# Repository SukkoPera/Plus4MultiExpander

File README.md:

# Plus4MultiExpander

Plus4MultiExpander is a port expander that allows multiple boards to be connected to the Expansion port of a Commodore 16, 116 and Plus/4.

## Summary
The main problem in making an Expansion port extender for the 264 line of computers is the complete unavailability of the original connector: these machines use a 50-pin connector with 2.00 mm pitch, which is nowhere to be found. This has been a problem since the old days, as you can see that even Solder of Synergy used different connectors when he made his [Expansion Port Splitter](https://plus4world.powweb.com/hardware/Expansionport_Splitter) in 1994. He used 50-pin connectors with 2.54 mm pitch, which in turn became rather uncommon in the following years, until they recently resurfaced from Chinese sellers.

This problem with the unavailability of the connector also affects [LittleSixteen](https://github.com/SukkoPera/LittleSixteen). Since one of the goals of that project is to fit into an unmodified C64-style case, Solder's connector of choice wouldn't help, as it is much larger than the opening on the case.

Of course, the opening on the case was made for the 44-pin 2.54 mm pitch connector the C64 uses, which for some reason is still available on the market, even from reliable manufacturers. It only has 6 pins less and since some of the pins on the 264 line are not used, I decided it was the best candidate for the new Expansion connector of the 264 line of computers.

## Design Notes
### Bus Buffers
Significant inspiration for the design of the expander comes from Solder's 1994 version. In particular, the expander integrates buffers for the address bus, in order to compensate for the increased bus capacitance. No buffers seem to be required on the data bus.

### Dropped Signals
As mentioned, 50-44=6 pins need to be dropped from the original connector:
- 3 are obvious, the unused pins: Z, AA, BB
- Since it is basically impossible to make an external RAM expansion, two more obvious drops would be the pins for the `/RAS` and `/CAS` signals. Unfortunately, `/RAS` is used by the 1551 drive paddle to (re)generate `PHI2`, but I see no reason for that, as `PHI2` is directly available on the connector. However, this is not enough of a reason to keep those signals: since in any case we will need to design a replacement paddle PCB with the new connector, we can also make it use that signal directly (This was even already done, as [TCBM2SD](https://github.com/ytmytm/plus4-tcbm2sd) can work as a 1551 paddle replacement and it doesn't need `/RAS`).
- For the remaining pin, even if `MUX` seems to only make sense for RAM expansions, it cannot be dropped since it is used as a clock signal by [SIDcards](https://github.com/SukkoPera/ReSeed) (and by my upcoming DigiMoooZ as well).
- After a long research, I rather decided to merge `/C2_LO` and `/C2_HI` into a single signal which I dubbed `/C2`. This seemed the best choice for a number or reasons:
  - Those signals are rarely used (I only know of [one cartridge](https://plus4world.powweb.com/sd.php?pid=14162) needing them).
  - When they are needed, they can sometimes be replaced by the new `/C2` signal.
  - If absolutely necessary, the original signals can be perfectly recreated very easily (see below).
- While the same approach could be applied to the `/C1_LO` and `/C1_HI` signals in order to spare yet one more pin, I opted not to do it, since these are much more frequently used and would require extra logic on every cartridge using them.
  
### Creation of /C2
Very simply:

    /C2 = /C2_LO and /C2_HI
    
This requires a simple AND gate (I used a common 74HCT08 logic chip to do that, whose spare gates were used to "buffer" some other signals). The original signals can be reconstructed as follows:
  
    /C2_LO = /C2 or /CS0
    /C2_HI = /C2 or /CS1
  
### Signal Reordering
Another decision I had to take was whether to leave the signals in the +4 order or reorder them in C64 style: since now a C64 cartridge can be physically connected to a +4, I thought it would be appropriate to put some effort into making that a bit safer from the electrical point of view, so I went with the reordering.

That left only three pins with possible conflicts:
- Pin 13 outputs `MUX`, while on the C64 it is an input for `/DMA`.
- Pin 8 outputs `AEC`, while on the C64 it is an input for `/GAME`.
- Pin D outputs the new `/C2` signal, but on the C64 this pin is an input for the `/NMI` signal.

Therefore, the current board is not completely safe in this regard, so **never plug a C64 cartridge into the expander**. In a future version series resistors might be added to prevent any mishaps.

### Audio Mixer
Since multiple audio cards might be plugged into the expander, sending their outputs to the `AUDIO_IN` pin, I added a passive mixer circuit to the expander.

This is constituted by resistors R1/R2/R3 and unfortunately it might have the side effect of lowering the output volume. To avoid this, you can enable sound output on a single connector: just mount a **single** 0 ohm resistor depending on which slot you want to enable: R1 for CN2, R2 for CN3 and R3 for CN4.

### Dimensions
The board has been made as large as possible while still being cheap to manufacture (which implies a maximum size of 10x10 cm). I wanted to fit at least 3 connectors and the spacing among them should be enough for standard-size cartridges.

If you have thicker cartridges, try putting them in the first or last slot, where you can probably gain some space by bending them slightly, or remove them from the case. Good-quality connectors will have no problems keeping them straight.

Of course, feel free to fork the project and make a larger version and/or with more connectors.

### Standoffs
I recommend mounting standoffs to keep the board straight: holes accept M2 screws and the recommended height is around 12 mm.

## Compatibility
Of course, the new connector means losing compatibility with all the existing boards. While that might make the whole thing sound crazy, it is not as bad as it seems: in the past years I have redesigned most of the C16/+4 expansion boards that are still relevant, and released all of those with an open source license. Therefore, it is generally a quick and easy job to update them with the new connector and release 44-pin versions. I have already done it with the following:
- [OpenC16Cart](https://github.com/SukkoPera/OpenC16Cart/releases/tag/v5_44pin)
- [PlusVIA](https://github.com/SukkoPera/PlusVIA/releases/tag/v2_44pin)
- [ReSeed](https://github.com/SukkoPera/ReSeed/releases/tag/v2_44pin)
- [SoundX](https://github.com/SukkoPera/SoundX/releases/tag/v2_44pin)

I have also made 44-pin versions of open-source projects from other authors:
- [ytmytm's TCBM2SD](https://github.com/SukkoPera/tcbm2sd-44pin)
- [Marko Šolajić's C264 Magic Cart](https://github.com/SukkoPera/c264-magic-cart-44pin)

I will slowly port other projects to the new connector as I have a need for them, but feel free to send me a request if you want something particular to be done, or just fork the project and do it yourself! That's the whole point of open source stuff and, as I said, it is generally an easy job.

In line of principle, it is also possible to make adapters between the two connectors, but of course the old-to-new variant is subject to the unavailability of the 50-pin connector. Nevertheless, I had [a go at it](https://github.com/SukkoPera/44to50).

### LittleSixteen
The [LittleSixteen project](https://github.com/SukkoPera/LittleSixteen) is planned to adopt the 44-pin connector in V5. 

## Releases
If you want to get this board produced, you are recommended to get [the latest release](https://github.com/SukkoPera/Plus4MultiExpander/releases) rather than the current git version, as the latter might be under development and is not guaranteed to be working.

Every release is accompanied by its Bill Of Materials (BOM) file and any relevant notes about it, which you are recommended to read carefully.

## License
The Plus4MultiExpander documentation, including the design itself, is copyright &copy; SukkoPera 2023 and is licensed under the [Creative Commons Attribution-NonCommercial-ShareAlike 4.0 International License](https://creativecommons.org/licenses/by-nc-sa/4.0/).

This documentation is distributed *as is* and WITHOUT ANY EXPRESS OR IMPLIED WARRANTIES whatsoever with respect to its functionality, operability or use, including, without limitation, any implied warranties OF MERCHANTABILITY, SATISFACTORY QUALITY, FITNESS FOR A PARTICULAR PURPOSE or infringement. We expressly disclaim any liability whatsoever for any direct, indirect, consequential, incidental or special damages, including, without limitation, lost revenues, lost profits, losses resulting from business interruption or loss of data, regardless of the form of action or legal theory under which the liability may be asserted, even if advised of the possibility or likelihood of such damages.

## Support the Project
If you want to get some boards manufactured, you can get them from PCBWay through this link:

You get my gratitude and cheap, professionally-made and good quality PCBs, I get some credit that will help with this and [other projects](https://www.pcbway.com/project/member/shareproject/?bmbid=41100). You won't even have to worry about the various PCB options, it's all pre-configured for you!

Also, if you still have to register, [you can use this link](https://www.pcbway.com/setinvite.aspx?inviteid=41100) to get some bonus initial credit (and yield me some more).

You can also buy me a coffee if you want:

## Thanks
* Solder of Synergy for making the original splitter.
* Haegar of Synergy for help and assistance.

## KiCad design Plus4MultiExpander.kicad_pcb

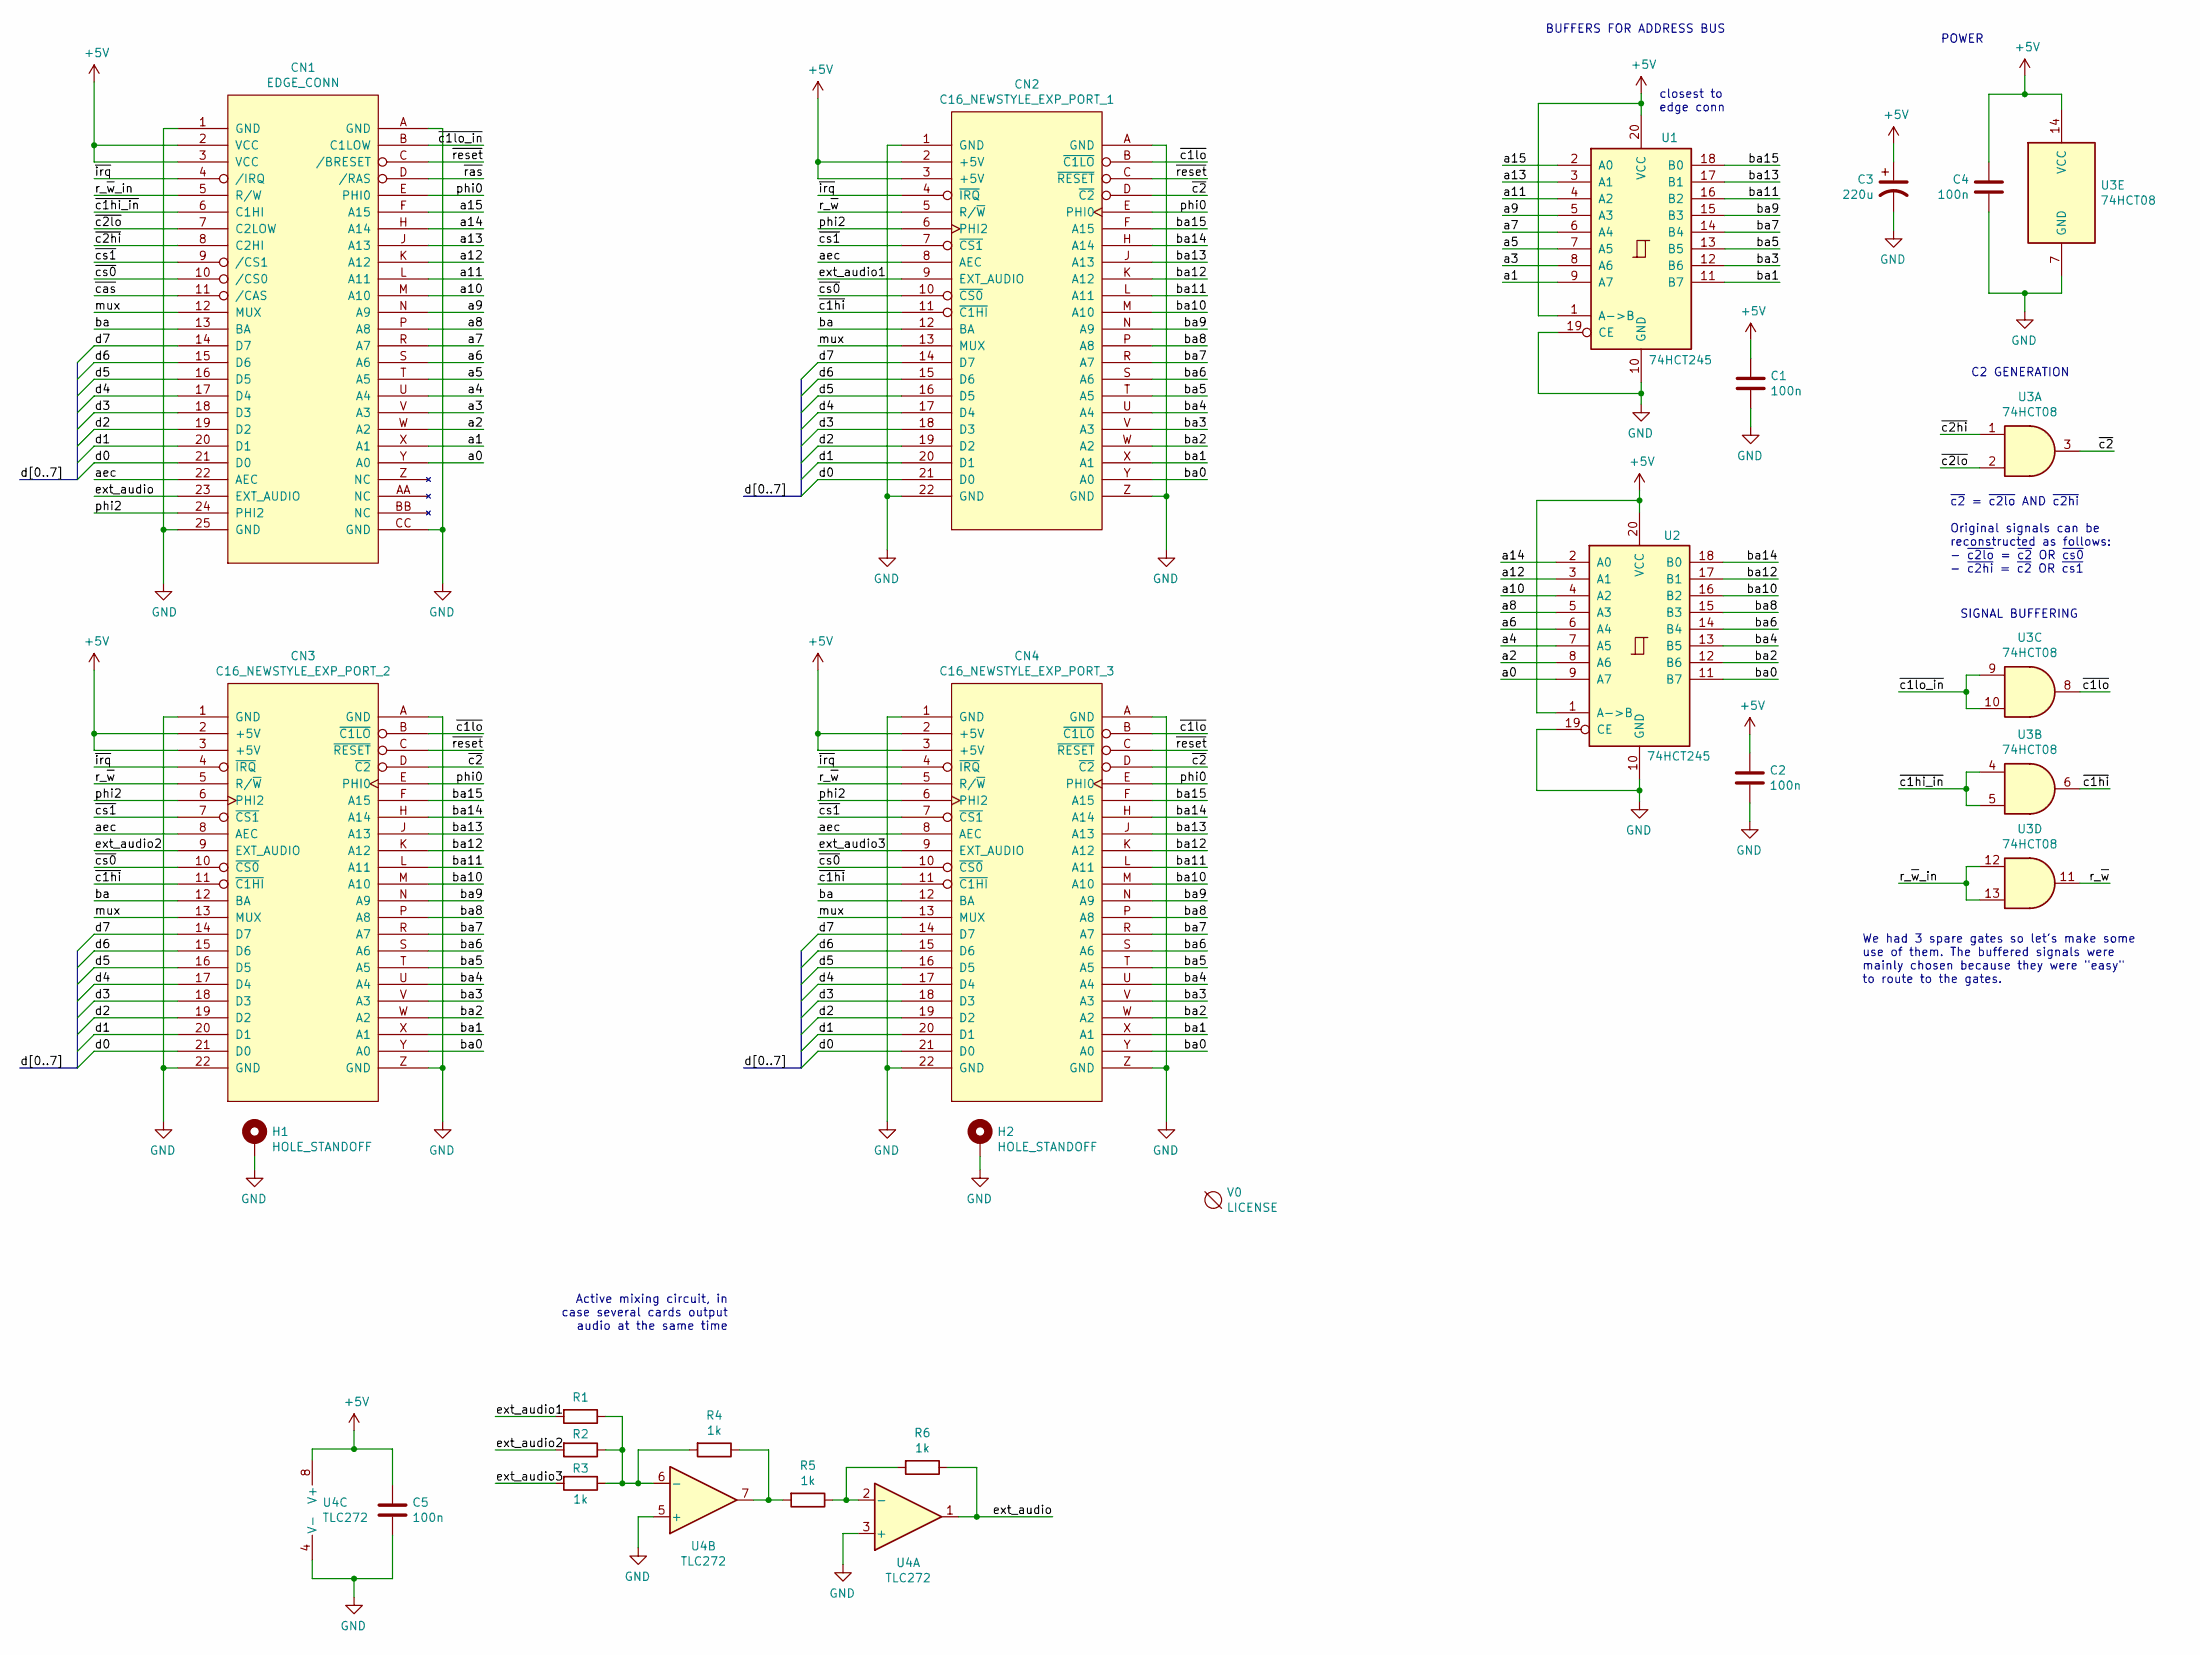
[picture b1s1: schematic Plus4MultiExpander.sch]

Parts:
C1, C2, C4, C5: 100n; C_Disc_D7.0mm_W2.5mm_P5.00mm
C3: 220u; CP_Radial_L11.5mm_D8.0mm_P3.5mm_Horizontal
CN1: EDGE_CONN; C16_Cart_Conn
CN2: C16_NEWSTYLE_EXP_PORT_1; C64-Cart-Socket-Vertical; MouserPN 571-5530843-4
CN3: C16_NEWSTYLE_EXP_PORT_2; C64-Cart-Socket-Vertical; MouserPN 571-5530843-4
CN4: C16_NEWSTYLE_EXP_PORT_3; C64-Cart-Socket-Vertical; MouserPN 571-5530843-4
H1, H2: HOLE_STANDOFF; MountingHole_2.5mm_Pad
R1, R2, R3, R4, R5, R6: 1k; R_Axial_DIN0204_L3.6mm_D1.6mm_P7.62mm_Horizontal
U1, U2: 74HCT245; DIP-20_W7.62mm_Socket_LongPads
U3: 74HCT08; DIP-14_W7.62mm_Socket_LongPads
U4: TLC272; DIP-8_W7.62mm_Socket_LongPads
V0: LICENSE; cc_by_nc_sa

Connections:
+5V: C1.1, C2.1, C3.1, C4.1, C5.1, CN1.2 (VCC), CN1.3 (VCC), CN2.2 (+5V), CN2.3 (+5V), CN3.2 (+5V), CN3.3 (+5V), CN4.2 (+5V), CN4.3 (+5V), U1.1 (A->B), U1.20 (VCC), U2.1 (A->B), U2.20 (VCC), U3.14 (VCC), U4.8 (V+)
/a0: CN1.Y (A0), U2.9 (A7)
/a1: CN1.X (A1), U1.9 (A7)
/a2: CN1.W (A2), U2.8 (A6)
/a3: CN1.V (A3), U1.8 (A6)
/a4: CN1.U (A4), U2.7 (A5)
/a5: CN1.T (A5), U1.7 (A5)
/a6: CN1.S (A6), U2.6 (A4)
/a7: CN1.R (A7), U1.6 (A4)
/a8: CN1.P (A8), U2.5 (A3)
/a9: CN1.N (A9), U1.5 (A3)
/a10: CN1.M (A10), U2.4 (A2)
/a11: CN1.L (A11), U1.4 (A2)
/a12: CN1.K (A12), U2.3 (A1)
/a13: CN1.J (A13), U1.3 (A1)
/a14: CN1.H (A14), U2.2 (A0)
/a15: CN1.F (A15), U1.2 (A0)
/aec: CN1.22 (AEC), CN2.8 (AEC), CN3.8 (AEC), CN4.8 (AEC)
/ba: CN1.13 (BA), CN2.12 (BA), CN3.12 (BA), CN4.12 (BA)
/ba0: CN2.Y (A0), CN3.Y (A0), CN4.Y (A0), U2.11 (B7)
/ba1: CN2.X (A1), CN3.X (A1), CN4.X (A1), U1.11 (B7)
/ba2: CN2.W (A2), CN3.W (A2), CN4.W (A2), U2.12 (B6)
/ba3: CN2.V (A3), CN3.V (A3), CN4.V (A3), U1.12 (B6)
/ba4: CN2.U (A4), CN3.U (A4), CN4.U (A4), U2.13 (B5)
/ba5: CN2.T (A5), CN3.T (A5), CN4.T (A5), U1.13 (B5)
/ba6: CN2.S (A6), CN3.S (A6), CN4.S (A6), U2.14 (B4)
/ba7: CN2.R (A7), CN3.R (A7), CN4.R (A7), U1.14 (B4)
/ba8: CN2.P (A8), CN3.P (A8), CN4.P (A8), U2.15 (B3)
/ba9: CN2.N (A9), CN3.N (A9), CN4.N (A9), U1.15 (B3)
/ba10: CN2.M (A10), CN3.M (A10), CN4.M (A10), U2.16 (B2)
/ba11: CN2.L (A11), CN3.L (A11), CN4.L (A11), U1.16 (B2)
/ba12: CN2.K (A12), CN3.K (A12), CN4.K (A12), U2.17 (B1)
/ba13: CN2.J (A13), CN3.J (A13), CN4.J (A13), U1.17 (B1)
/ba14: CN2.H (A14), CN3.H (A14), CN4.H (A14), U2.18 (B0)
/ba15: CN2.F (A15), CN3.F (A15), CN4.F (A15), U1.18 (B0)
/d0: CN1.21 (D0), CN2.21 (D0), CN3.21 (D0), CN4.21 (D0)
/d1: CN1.20 (D1), CN2.20 (D1), CN3.20 (D1), CN4.20 (D1)
/d2: CN1.19 (D2), CN2.19 (D2), CN3.19 (D2), CN4.19 (D2)
/d3: CN1.18 (D3), CN2.18 (D3), CN3.18 (D3), CN4.18 (D3)
/d4: CN1.17 (D4), CN2.17 (D4), CN3.17 (D4), CN4.17 (D4)
/d5: CN1.16 (D5), CN2.16 (D5), CN3.16 (D5), CN4.16 (D5)
/d6: CN1.15 (D6), CN2.15 (D6), CN3.15 (D6), CN4.15 (D6)
/d7: CN1.14 (D7), CN2.14 (D7), CN3.14 (D7), CN4.14 (D7)
/ext_audio: CN1.23 (EXT_AUDIO), R6.1, U4.1
/ext_audio1: CN2.9 (EXT_AUDIO), R1.2
/ext_audio2: CN3.9 (EXT_AUDIO), R2.2
/ext_audio3: CN4.9 (EXT_AUDIO), R3.2
/mux: CN1.12 (MUX), CN2.13 (MUX), CN3.13 (MUX), CN4.13 (MUX)
/phi0: CN1.E (PHI0), CN2.E (PHI0), CN3.E (PHI0), CN4.E (PHI0)
/phi2: CN1.24 (PHI2), CN2.6 (PHI2), CN3.6 (PHI2), CN4.6 (PHI2)
/r_~w: CN2.5 (R/~W), CN3.5 (R/~W), CN4.5 (R/~W), U3.11
/r_~w~_in: CN1.5 (R/W), U3.12, U3.13
/~c1hi: CN2.11 (~C1HI), CN3.11 (~C1HI), CN4.11 (~C1HI), U3.6
/~c1hi_in: CN1.6 (C1HI), U3.4, U3.5
/~c1lo: CN2.B (~C1LO), CN3.B (~C1LO), CN4.B (~C1LO), U3.8
/~c1lo_in: CN1.B (C1LOW), U3.9, U3.10
/~c2: CN2.D (~C2), CN3.D (~C2), CN4.D (~C2), U3.3
/~c2hi: CN1.8 (C2HI), U3.1
/~c2lo: CN1.7 (C2LOW), U3.2
/~cas: CN1.11 (/CAS)
/~cs0: CN1.10 (/CS0), CN2.10 (~CS0), CN3.10 (~CS0), CN4.10 (~CS0)
/~cs1: CN1.9 (/CS1), CN2.7 (~CS1), CN3.7 (~CS1), CN4.7 (~CS1)
/~irq: CN1.4 (/IRQ), CN2.4 (~IRQ), CN3.4 (~IRQ), CN4.4 (~IRQ)
/~ras: CN1.D (/RAS)
/~reset: CN1.C (/BRESET), CN2.C (~RESET), CN3.C (~RESET), CN4.C (~RESET)
GND: C1.2, C2.2, C3.2, C4.2, C5.2, CN1.1 (GND), CN1.25 (GND), CN1.A (GND), CN1.CC (GND), CN2.1 (GND), CN2.22 (GND), CN2.A (GND), CN2.Z (GND), CN3.1 (GND), CN3.22 (GND), CN3.A (GND), CN3.Z (GND), CN4.1 (GND), CN4.22 (GND), CN4.A (GND), CN4.Z (GND), H1.1, H2.1, U1.10 (GND), U1.19 (CE), U2.10 (GND), U2.19 (CE), U3.7 (GND), U4.3 (+), U4.4 (V-), U4.5 (+)
unnamed: R1.1, R2.1, R3.1, R4.2, U4.6 (-)
unnamed: R4.1, R5.2, U4.7
unnamed: R5.1, R6.2, U4.2 (-)

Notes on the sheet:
closest to edge conn
~c2~ = ~c2lo~ AND ~c2hi~ Original signals can be reconstructed as follows: - ~c2lo~ = ~c2~ OR ~cs0~ - ~c2hi~ = ~c2~ OR ~cs1~
BUFFERS FOR ADDRESS BUS
C2 GENERATION
POWER
Active mixing circuit, in case several cards output audio at the same time
SIGNAL BUFFERING
We had 3 spare gates so let's make some use of them. The buffered signals were mainly chosen because they were "easy" to route to the gates.

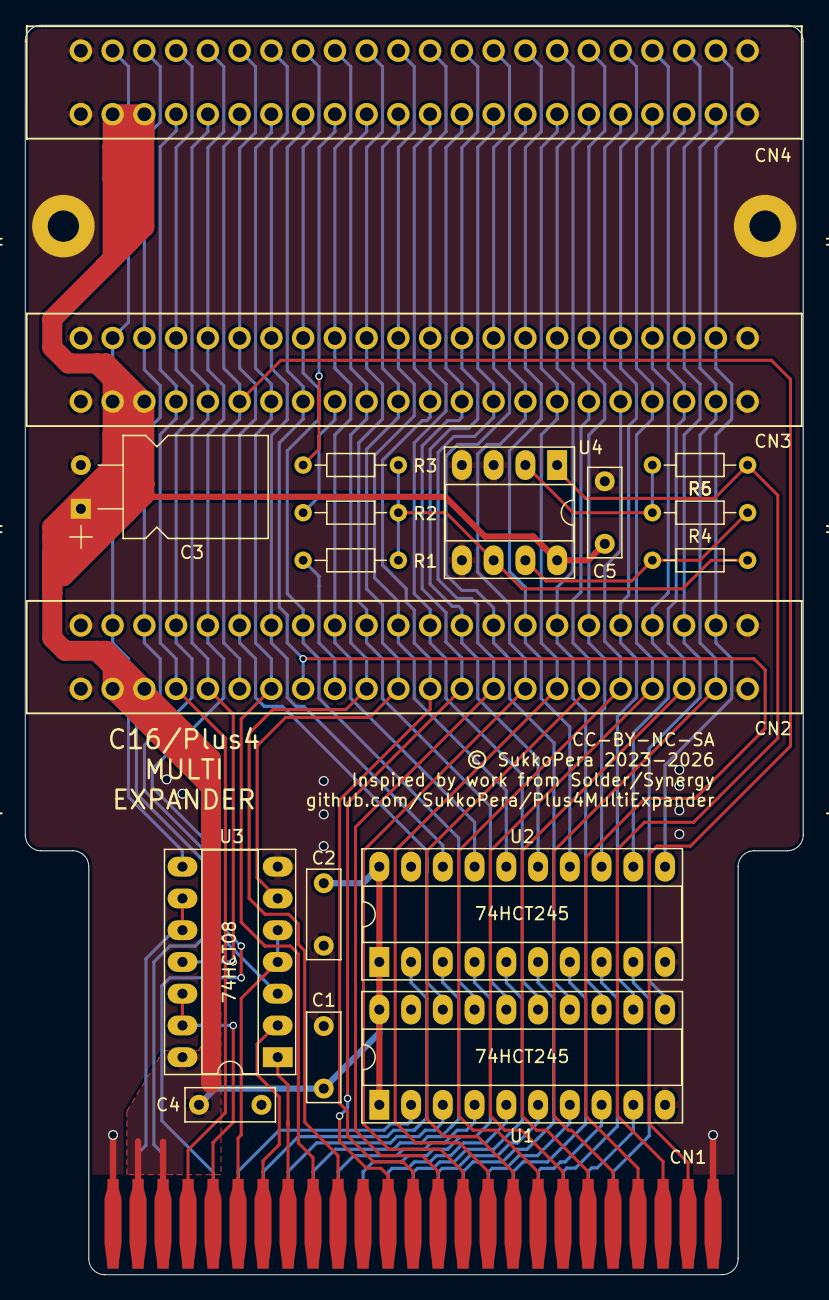
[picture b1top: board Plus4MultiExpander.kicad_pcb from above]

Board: 2 copper layers, 62.2 x 99.9 mm, 22 parts (1 on the bottom side), 67 nets.

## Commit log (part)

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2023-07-29 Initial commit - Schematics should be OK, board must be rerouted allowing for slack space between carts
2023-07-29 Space connectors properly Needs cleanup but board is there
2023-07-29 Honing
2023-07-29 New edge connector with larger pads
2023-07-29 More honing
2023-07-29 Add 3D model of connector
2023-08-03 Tidy up silkscreen
2023-08-03 Add credits and license
2023-09-07 Generate /C2 with NAND gate
2023-09-07 Add standoff holes
2023-09-10 Add mixing resistors for EXT_AUDIO
2023-09-10 Add working proof for C2 generation
2023-09-24 Switch to AND gate and buffer some more signals
2023-09-24 Buffer R/W instead of PHI0
2023-09-27 Better routing
2023-09-29 New pin mapping
2023-09-30 Refinements
2023-10-03 Final touches
2026-02-27 Add README
2026-02-27 Add renders
2026-02-27 Update PCBWay link
2026-03-02 Add PlusVIA link
    Updated compatibility section to include PlusVIA link and clarify 44-pin versions.
2026-03-02 Active mixer prototype
2026-03-03 Add ReSeed 44-pin link in README
    Updated compatibility section to include ReSeed with a link.
2026-03-04 Add acknowledgments
2026-03-04 Add link to 44-pin version of SoundX V2

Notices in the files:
Plus4MultiExpander.kicad_pcb:
Licensed under CC BY-NC-SA 4.0
© SukkoPera 2023-2026
